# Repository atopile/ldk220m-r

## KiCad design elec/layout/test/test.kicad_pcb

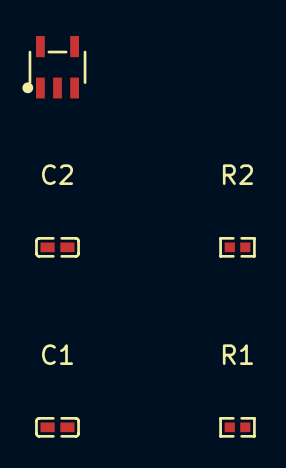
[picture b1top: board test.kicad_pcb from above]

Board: 2 copper layers, 5 parts (0 on the bottom side), 4 nets, no tracks yet.

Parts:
C1, C2: 1µF ±10% 25V X5R; C0402-b3ef17
R1: 5.6kΩ ±1% 62.5mW; R0402-56259e
R2: 10kΩ ±1% 62.5mW; R0402-56259e
U1: SOT-23-5_L3.0-W1.7-P0.95-LS2.8-BL

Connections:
ADJ_NC: R1.1, R2.2, U1.4
EN: C1.1, U1.1, U1.3
OUT: C2.1, R2.1, U1.5
gnd: C1.2, C2.2, R1.2, U1.2

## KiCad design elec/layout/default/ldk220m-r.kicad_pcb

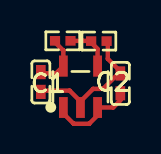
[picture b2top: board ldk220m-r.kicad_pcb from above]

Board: 2 copper layers, 5 parts (0 on the bottom side), 4 nets.

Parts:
C1, C2: 1µF ±10% 25V X5R; C0402-b3ef17
R1, R2: 10kΩ ±1% 62.5mW; R0402-56259e
U1: SOT-23-5_L3.0-W1.7-P0.95-LS2.8-BL

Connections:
ADJ_NC: R1.2, R2.1, U1.4
EN: C1.1, U1.1, U1.3
OUT: C2.1, R1.1, U1.5
gnd: C1.2, C2.2, R2.2, U1.2

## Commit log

2024-02-13 Configure project
2024-02-13 added doc strings
2024-02-15 layout
2024-02-29 add support for equations
2024-02-29 increase i_q
2024-04-16 fix assertion for ldo
2025-01-27 removed the dreaded snowman, saved layout with kicad V8
2025-01-27 Ran build to update atopile addresses in layout
2025-03-08 Update to 0.3 syntax, use regulator defintion from library
2025-03-19 update layout for kicad9, fix default entry for layout reuse to work
